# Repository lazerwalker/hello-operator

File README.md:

# Hello, Operator!

This is the source code that powers [Hello, Operator!](http://lazerwalker.com/hellooperator).

## Setup

1. Be sure you're using Node version `0.12.x`. This is because `node-serialport` won't compile on OS X on anything newer. I personally use [nvm](https://github.com/creationix/nvm) to manage this; it is also specified in `package.json`. It is possible newer versions of Node will work in non-OS X environments, but that has not been tested.

2. Install coffee-script globally: `npm install -g coffee-script`

3. Git clone this repo: `git clone git@github.com:lazerwalker/switchboard.git`

4. Install dependencies: `npm install`

5. Modify `runner.coffee` to include the appropriate game interfaces with appropriate options (e.g. Arduino USB serial ports)

6. Run `coffee runner.coffee`

## Audio

This repository does not currently contain the audio files used in the game. In order to play it, the "audio" folder will need data in the following structure: 

```
/ audio 
  / Ethel
    / Rosemary.aiff
    / Donald.aiff
  / Rosemary
    / Ethel.aiff
```

There must be a folder for every character in the game (defined in `game.coffee`), and each character's folder must contain an audio file called `{name}.aiff` for every other name.

It is likely that the actual audio used in the game itself will be released under a Creative Commons license at some point, but that is not the case at this time. Currently, this is accomplished via a private submodule; you will likely want to create your own submodule and update your internal git structure to point to it.

## iOS Project

To run the included iPad version of the game, you need to compile the codebase into a single JS file. Run `./compile` in the root directory, then run and compile the Xcode workspace that lives in the `ios` subdirectory. This will only work on OS X with the latest version of Xcode.

By default, the iOS app will just run the game itself. You can also use it as a remote client to a server-run instance of the game; that requires a deployment of the server component, which isn't currently documented. Sorry about that.

## Caveats

This codebase isn't in great shape. It's persisted across three very different hardware iterations, and probably should have been rewritten from the ground up by now. Due to the severe time constraints surrounding this project, software engineering quality has generally taken second place to hardware fabrication. There's a lot of bad code and a lot of dead code. Some of the more recent code does have tests, which can be run via `npm test`.

Similarly, and perhaps more relevant, this documentation is terrible. If you actually intend on getting this up and running, you'll probably need to bug me personally. I'm not exactly sure who I expect to actively try to use this repo, but in general I'm cool with people contacting me with questions about it. Feel free to shoot me an email at hellooperator@lazerwalker.com, or tweet at me @lazerwalker.

## License

This project is licensed under the MIT License.

Copyright (c) 2014-2016 Mike Lazer-Walker and MIT Media Lab

Permission is hereby granted, free of charge, to any person obtaining a copy of this software and associated documentation files (the "Software"), to deal in the Software without restriction, including without limitation the rights to use, copy, modify, merge, publish, distribute, sublicense, and/or sell copies of the Software, and to permit persons to whom the Software is furnished to do so, subject to the following conditions:

The above copyright notice and this permission notice shall be included in all copies or substantial portions of the Software.

THE SOFTWARE IS PROVIDED "AS IS", WITHOUT WARRANTY OF ANY KIND, EXPRESS OR IMPLIED, INCLUDING BUT NOT LIMITED TO THE WARRANTIES OF MERCHANTABILITY, FITNESS FOR A PARTICULAR PURPOSE AND NONINFRINGEMENT. IN NO EVENT SHALL THE AUTHORS OR COPYRIGHT HOLDERS BE LIABLE FOR ANY CLAIM, DAMAGES OR OTHER LIABILITY, WHETHER IN AN ACTION OF CONTRACT, TORT OR OTHERWISE, ARISING FROM, OUT OF OR IN CONNECTION WITH THE SOFTWARE OR THE USE OR OTHER DEALINGS IN THE SOFTWARE.

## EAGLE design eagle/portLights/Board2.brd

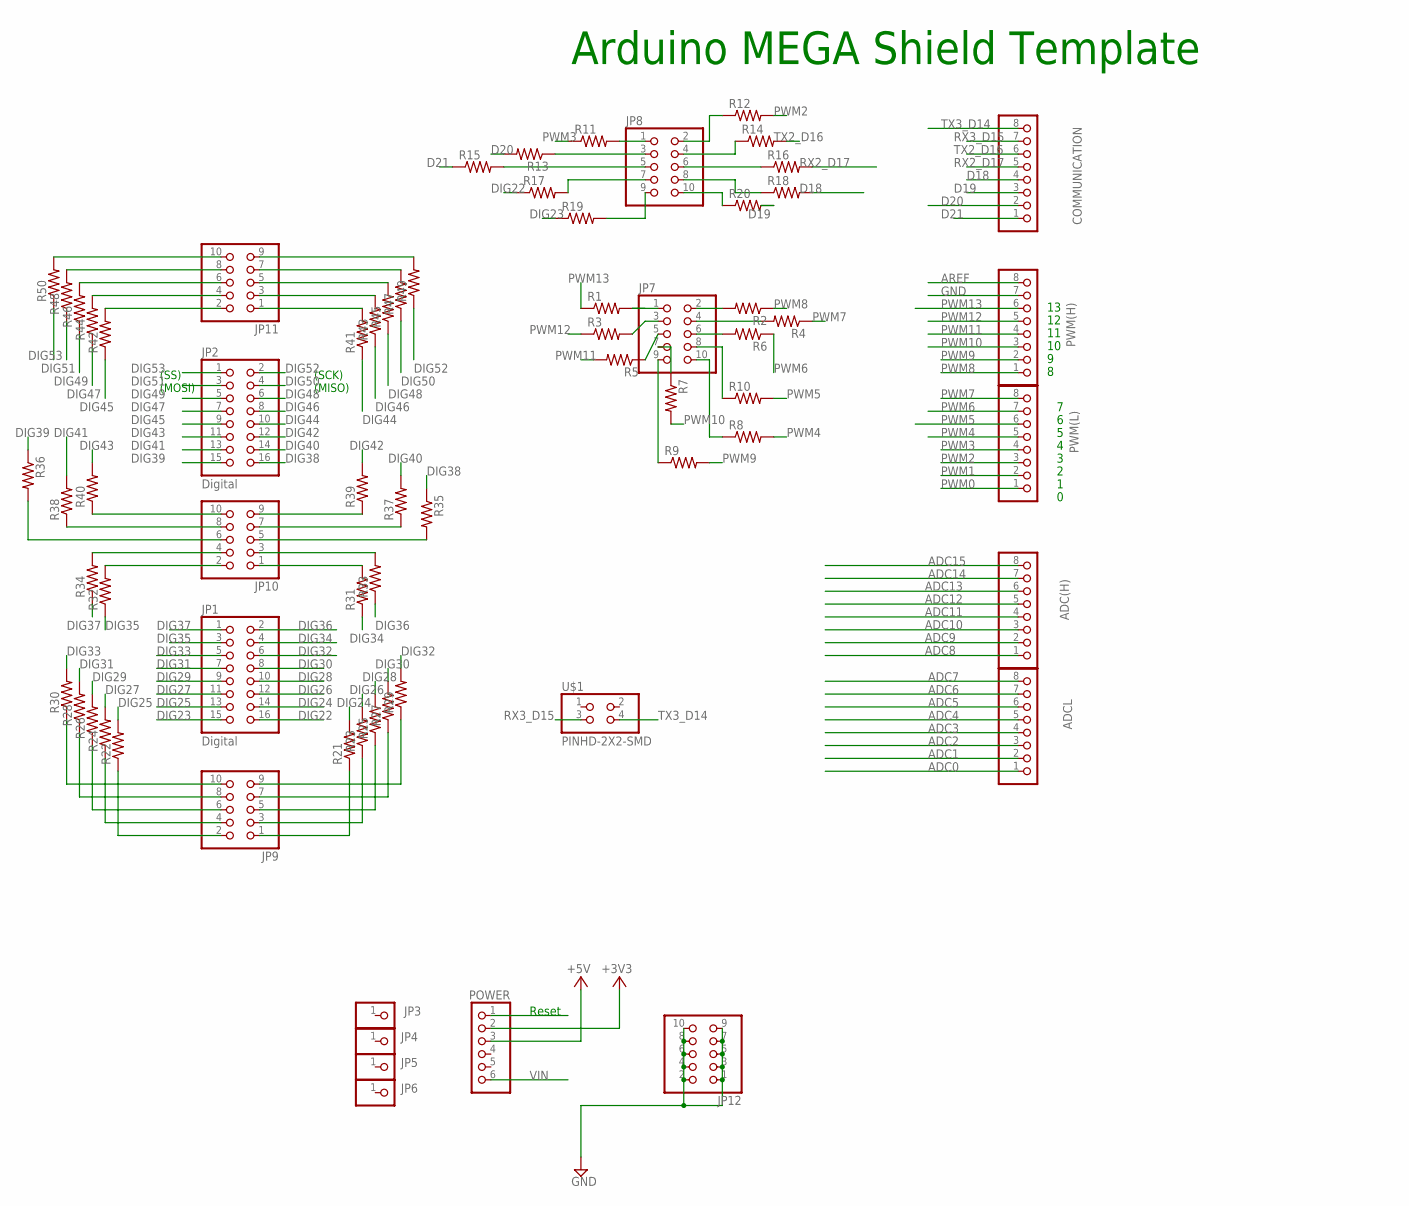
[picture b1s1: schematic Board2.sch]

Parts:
ADC(H): PINHD-1X8; 1X08
ADCL: PINHD-1X8; 1X08
COMMUNICATION: PINHD-1X8; 1X08
JP1, JP2: Digital; 2X08
JP3, JP4, JP5, JP6: PINHD-1X1; 1X01
JP7, JP8, JP9, JP10, JP11, JP12: PINHD-2X5SMT; 2X05_SMT
POWER: PINHD-1X6; 1X06
PWM(H): PINHD-1X8; 1X08
PWM(L): PINHD-1X8; 1X08
R1, R2, R3, R4, R5, R6, R7, R8, R9, R10, R11, R12, R13, R14, R15, R16, R17, R18, R19, R20, R21, R22, R23, R24, R25, R26, R27, R28, R29, R30, R31, R32, R33, R34, R35, R36, R37, R38, R39, R40, R41, R42, R43, R44, R45, R46, R47, R48, R49, R50: R-US_M1206; M1206
U$1: PINHD-2X2-SMD; 2X02SMD

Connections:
+3V3: POWER.2
+5V: POWER.3
ADC0: ADCL.1
ADC1: ADCL.2
ADC2: ADCL.3
ADC3: ADCL.4
ADC4: ADCL.5
ADC5: ADCL.6
ADC6: ADCL.7
ADC7: ADCL.8
ADC8: ADC(H).1
ADC9: ADC(H).2
ADC10: ADC(H).3
ADC11: ADC(H).4
ADC12: ADC(H).5
ADC13: ADC(H).6
ADC14: ADC(H).7
ADC15: ADC(H).8
AREF: PWM(H).8
D18: COMMUNICATION.4, R18.2
D19: COMMUNICATION.3, R20.2
D20: COMMUNICATION.2, R13.2
D21: COMMUNICATION.1, R15.1
DIG22: JP1.16, R17.1
DIG23: JP1.15, R19.1
DIG24: JP1.14, R21.2
DIG25: JP1.13, R22.2
DIG26: JP1.12, R23.2
DIG27: JP1.11, R24.2
DIG28: JP1.10, R25.2
DIG29: JP1.9, R26.2
DIG30: JP1.8, R27.2
DIG31: JP1.7, R28.2
DIG32: JP1.6, R29.2
DIG33: JP1.5, R30.2
DIG34: JP1.4, R31.1
DIG35: JP1.3, R32.1
DIG36: JP1.2, R33.1
DIG37: JP1.1, R34.1
DIG38: JP2.16, R35.1
DIG39: JP2.15, R36.1
DIG40: JP2.14, R37.2
DIG41: JP2.13, R38.2
DIG42: JP2.12, R39.2
DIG43: JP2.11, R40.2
DIG44: JP2.10, R41.1
DIG45: JP2.9, R42.1
DIG46: JP2.8, R43.1
DIG47: JP2.7, R44.1
DIG48: JP2.6, R45.1
DIG49: JP2.5, R46.1
DIG50: JP2.4, R47.1
DIG51: JP2.3, R48.1
DIG52: JP2.2, R49.1
DIG53: JP2.1, R50.1
GND: JP12.1, JP12.2, JP12.3, JP12.4, JP12.5, JP12.6, JP12.7, JP12.8, JP12.9, JP12.10, PWM(H).7
unnamed: JP7.3, R3.2
unnamed: JP7.5, R5.1
unnamed: JP7.7, R7.1
unnamed: JP7.9, R9.1
unnamed: JP7.4, R4.2
unnamed: JP8.5, R15.2
unnamed: JP7.6, R6.2
unnamed: JP7.2, R2.2
unnamed: JP7.8, R10.1
unnamed: JP8.1, R11.2
unnamed: JP8.2, R12.1
unnamed: JP7.10, R8.1
unnamed: JP8.7, R17.2
unnamed: JP10.6, R36.2
unnamed: JP8.6, R16.1
unnamed: JP10.5, R35.2
unnamed: JP8.4, R14.1
unnamed: JP9.2, R22.1
unnamed: JP7.1, R1.2
unnamed: JP8.10, R20.1
unnamed: JP9.4, R24.1
unnamed: JP9.6, R26.1
unnamed: JP9.8, R28.1
unnamed: JP9.10, R30.1
unnamed: JP9.1, R21.1
unnamed: JP9.3, R23.1
unnamed: JP9.5, R25.1
unnamed: JP9.7, R27.1
unnamed: JP9.9, R29.1
unnamed: JP10.3, R33.2
unnamed: JP10.1, R31.2
unnamed: JP10.2, R32.2
unnamed: JP10.4, R34.2
unnamed: JP10.7, R37.1
unnamed: JP10.9, R39.1
unnamed: JP10.8, R38.1
unnamed: JP10.10, R40.1
unnamed: JP11.9, R49.2
unnamed: JP11.7, R47.2
unnamed: JP11.5, R45.2
unnamed: JP11.3, R43.2
unnamed: JP11.1, R41.2
unnamed: JP11.2, R42.2
unnamed: JP11.4, R44.2
unnamed: JP11.6, R46.2
unnamed: JP11.8, R48.2
unnamed: JP11.10, R50.2
unnamed: JP8.9, R19.2
PWM0: PWM(L).1
PWM1: PWM(L).2
PWM2: PWM(L).3, R12.2
PWM3: PWM(L).4, R11.1
PWM4: PWM(L).5, R8.2
PWM5: PWM(L).6, R10.2
PWM6: PWM(L).7, R6.1
PWM7: PWM(L).8, R4.1
PWM8: PWM(H).1, R2.1
PWM9: PWM(H).2, R9.2
PWM10: PWM(H).3, R7.2
PWM11: PWM(H).4, R5.2
PWM12: PWM(H).5, R3.1
PWM13: PWM(H).6, R1.1
RESET: POWER.1
RX1_D19: JP8.8, R18.1
RX2_D17: COMMUNICATION.5, R16.2
RX3_D15: COMMUNICATION.7, U$1.3
RX4_D14: JP8.3, R13.1
TX2_D16: COMMUNICATION.6, R14.2
TX3_D14: COMMUNICATION.8, U$1.4
VIN: POWER.6

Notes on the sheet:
Arduino MEGA Shield Template
(SS)
(MOSI)
(SCK)
(MISO)
Reset

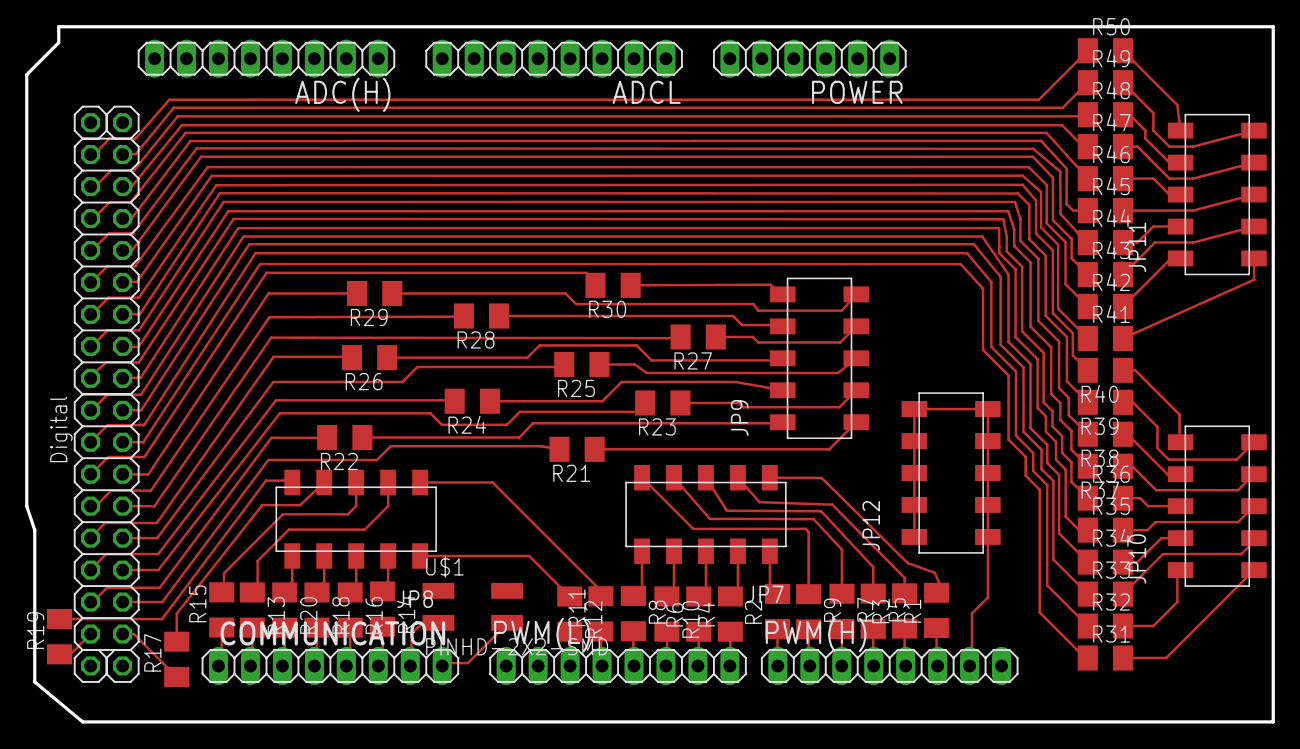
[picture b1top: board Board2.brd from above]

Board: 2 copper layers, 99.1 x 55.2 mm, 69 parts (0 on the bottom side), 103 nets.

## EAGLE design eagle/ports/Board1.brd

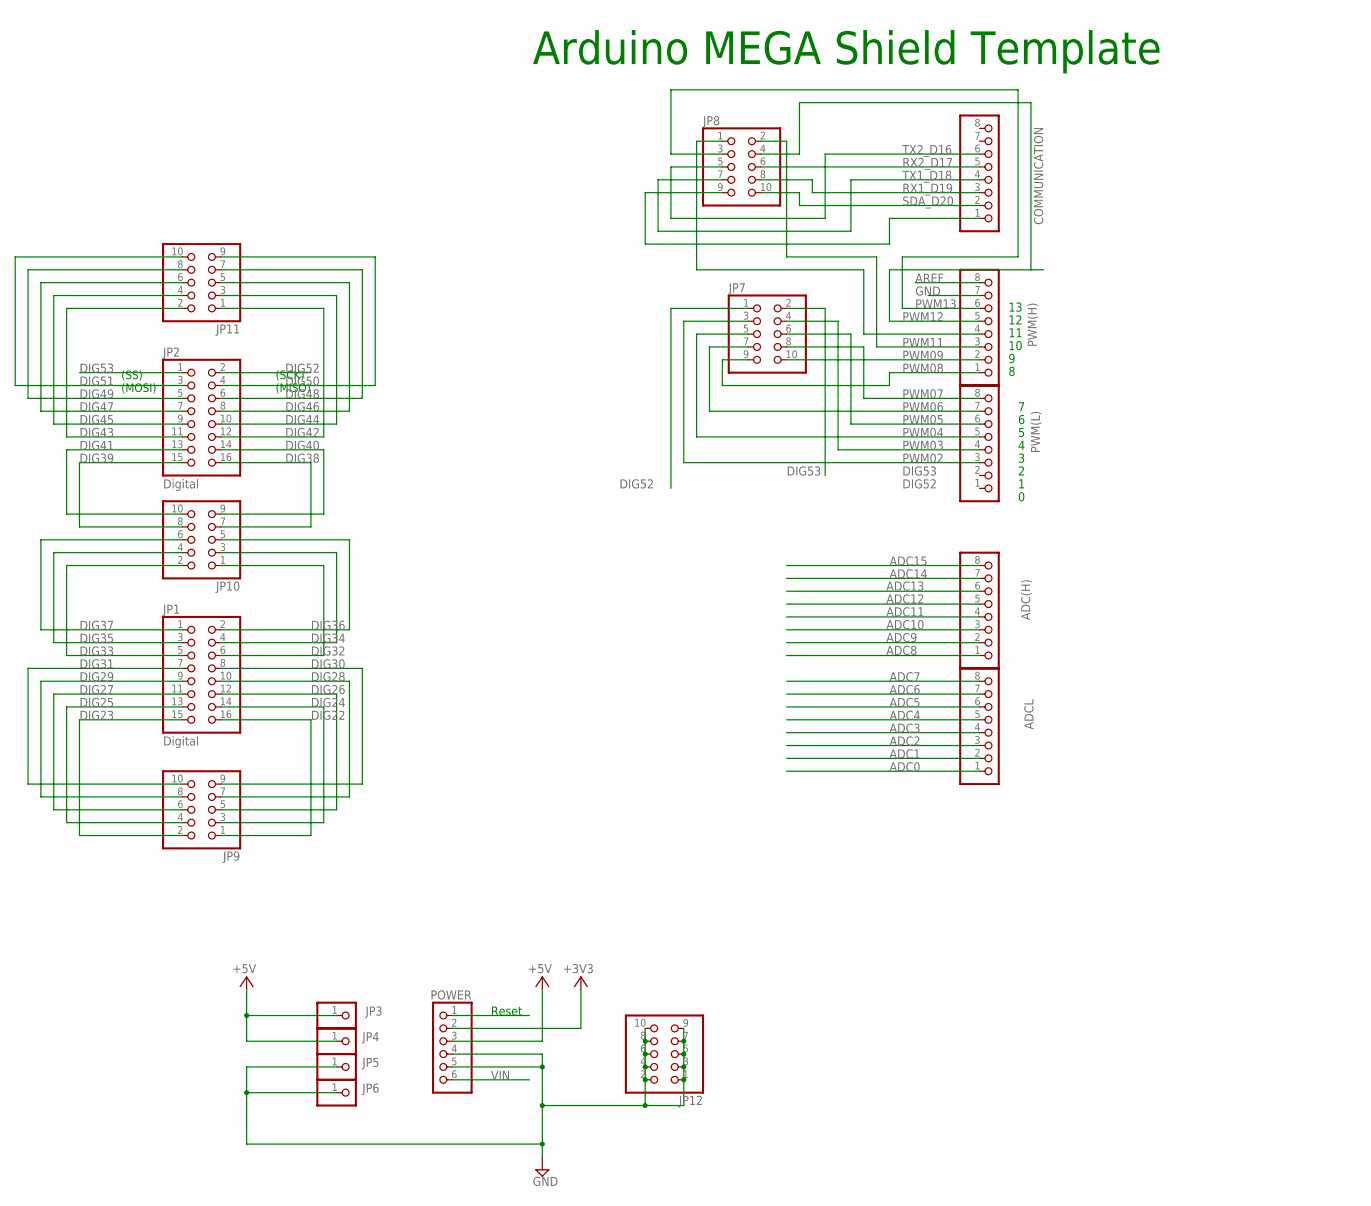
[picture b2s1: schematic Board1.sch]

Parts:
ADC(H): PINHD-1X8; 1X08
ADCL: PINHD-1X8; 1X08
COMMUNICATION: PINHD-1X8; 1X08
JP1, JP2: Digital; 2X08
JP3, JP4, JP5, JP6: PINHD-1X1; 1X01
JP7, JP8, JP9, JP10, JP11, JP12: PINHD-2X5SMT; 2X05_SMT
POWER: PINHD-1X6; 1X06
PWM(H): PINHD-1X8; 1X08
PWM(L): PINHD-1X8; 1X08

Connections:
+3V3: POWER.2
+5V: JP3.1, JP4.1, POWER.3
ADC0: ADCL.1
ADC1: ADCL.2
ADC2: ADCL.3
ADC3: ADCL.4
ADC4: ADCL.5
ADC5: ADCL.6
ADC6: ADCL.7
ADC7: ADCL.8
ADC8: ADC(H).1
ADC9: ADC(H).2
ADC10: ADC(H).3
ADC11: ADC(H).4
ADC12: ADC(H).5
ADC13: ADC(H).6
ADC14: ADC(H).7
ADC15: ADC(H).8
AREF: PWM(H).8
DIG22: JP1.16, JP9.1
DIG23: JP1.15, JP9.2
DIG24: JP1.14, JP9.3
DIG25: JP1.13, JP9.4
DIG26: JP1.12, JP9.5
DIG27: JP1.11, JP9.6
DIG28: JP1.10, JP9.7
DIG29: JP1.9, JP9.8
DIG30: JP1.8, JP9.9
DIG31: JP1.7, JP9.10
DIG32: JP1.6, JP10.1
DIG33: JP1.5, JP10.2
DIG34: JP1.4, JP10.3
DIG35: JP1.3, JP10.4
DIG36: JP1.2, JP10.5
DIG37: JP1.1, JP10.6
DIG38: JP2.16, JP10.7
DIG39: JP2.15, JP10.8
DIG40: JP2.14, JP10.9
DIG41: JP2.13, JP10.10
DIG42: JP2.12, JP11.1
DIG43: JP2.11, JP11.2
DIG44: JP2.10, JP11.3
DIG45: JP2.9, JP11.4
DIG46: JP2.8, JP11.5
DIG47: JP2.7, JP11.6
DIG48: JP2.6, JP11.7
DIG49: JP2.5, JP11.8
DIG50: JP2.4, JP11.9
DIG51: JP2.3, JP11.10
DIG52: JP2.2, JP7.1
DIG53: JP2.1, JP7.2
GND: JP5.1, JP6.1, JP12.1, JP12.2, JP12.3, JP12.4, JP12.5, JP12.6, JP12.7, JP12.8, JP12.9, JP12.10, POWER.4, POWER.5, PWM(H).7
unnamed: COMMUNICATION.2, JP8.10
PWM02: JP7.3, PWM(L).3
PWM03: JP7.4, PWM(L).4
PWM04: JP7.5, PWM(L).5
PWM05: JP7.6, PWM(L).6
PWM06: JP7.7, PWM(L).7
PWM07: JP7.8, PWM(L).8
PWM08: JP7.9, PWM(H).1
PWM09: JP7.10, PWM(H).2
PWM10: JP8.1, PWM(H).4
PWM11: JP8.2, PWM(H).3
PWM12: JP8.4, PWM(H).5
PWM13: JP8.3, PWM(H).6
RESET: POWER.1
RX1_D19: COMMUNICATION.3, JP8.8
RX2_D17: COMMUNICATION.5, JP8.6
SDA_D20: COMMUNICATION.1, JP8.9
TX1_D18: COMMUNICATION.4, JP8.7
TX2_D16: COMMUNICATION.6, JP8.5
VIN: POWER.6

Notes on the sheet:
Arduino MEGA Shield Template
(SS)
(MOSI)
(SCK)
(MISO)
Reset

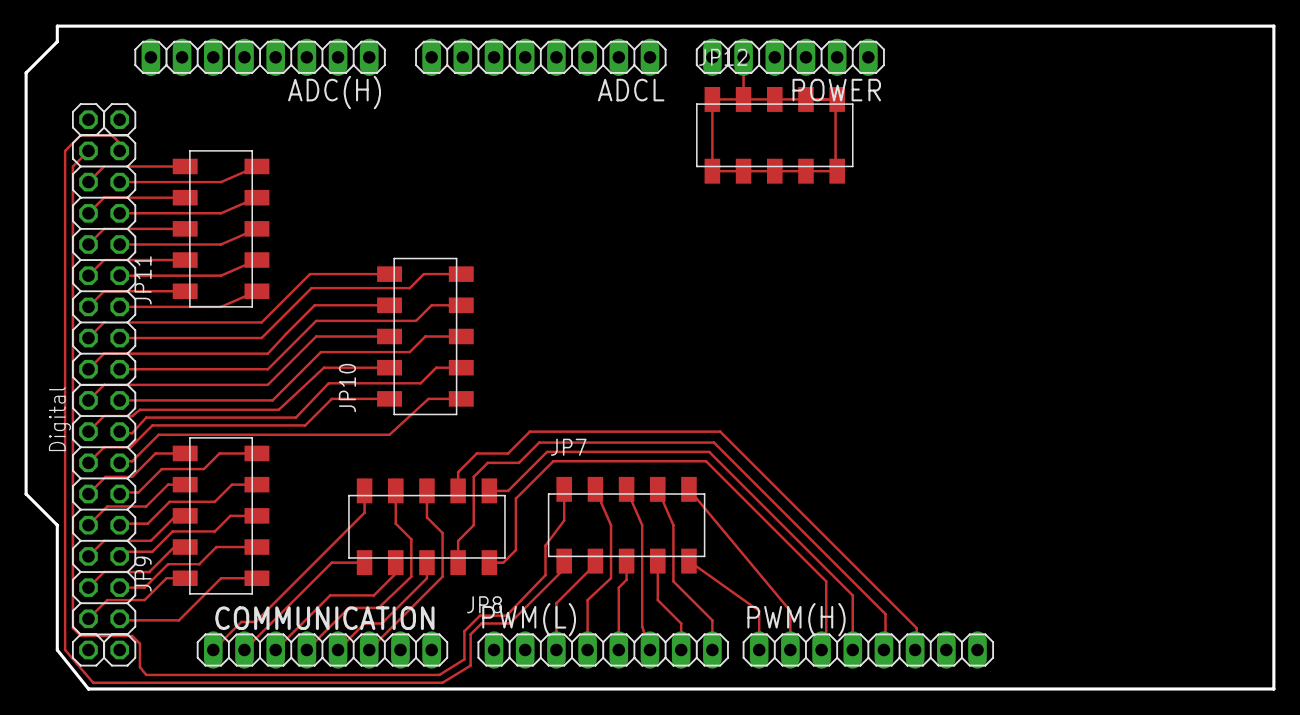
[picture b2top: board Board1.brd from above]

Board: 2 copper layers, 101.6 x 54.0 mm, 18 parts (0 on the bottom side), 52 nets.

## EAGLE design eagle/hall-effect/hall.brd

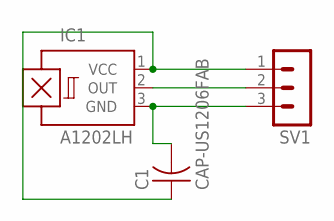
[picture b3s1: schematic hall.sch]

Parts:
C1: CAP-US1206FAB; C1206FAB
IC1: A1202LH; SOT23-W
SV1: MA03-1

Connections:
unnamed: C1.1, IC1.1 (VCC), SV1.1
unnamed: IC1.2 (OUT), SV1.2
unnamed: C1.2, IC1.3 (GND), SV1.3

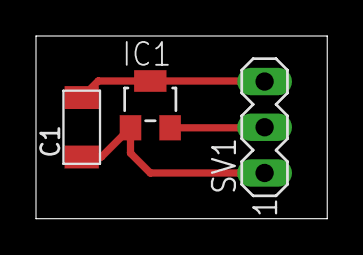
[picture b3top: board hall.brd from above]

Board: 2 copper layers, 16.2 x 10.1 mm, 3 parts (0 on the bottom side), 3 nets.

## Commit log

2014-10-11 Arduino script sends JSON
2014-10-11 CoffeeScript can read from serial port
2014-10-11 Change JSON format
2014-10-11 Fix bug interfering when multiple pins connected
2014-10-11 Install understore.js
2014-10-11 Switch from newline to carriage return
2014-10-11 Can pick up callers
2014-10-11 Add matching logic
2014-10-11 Don't let you double-pick-up
2014-10-11 Fix malformed serial parsing errors
2014-10-11 Switch from naive pin mapping to fuller objects
2014-10-11 Don't start call with people who are already busy
2014-10-11 2 rows of phones
2014-10-11 Can play audio
2014-10-11 Turn LEDs on/off as appropriate
2014-10-12 Tweaks to LED logic
2014-10-12 Make output easily togglable
2014-10-12 Don't let you complete the circuit without knowing who it is
2014-10-12 Remove LED testing code
2014-10-12 Change highest pin in arduino code
2015-08-24 Add gitignore
2015-08-24 move arduino stuff into its own folder
2015-08-24 Preliminary split-out interface work
2015-08-24 gitignore node_modules
2015-08-24 Game is playable with console interface
2015-08-24 Add (untested) WebsocketInterface
2015-08-24 Add iOS project
2015-08-24 Add SwiftWebSocket
2015-08-30 iOS app has a grid of things
2015-08-30 iOS gitignore
2015-08-30 Go from 8 to 10 ports on iOS
2015-08-30 Bind items
2015-08-30 Can set name and LED status
2015-08-30 Abstract game logic from game runner
2015-08-30 JS talks to iOS
2015-08-30 Game connection can talk to screen a bit
2015-08-31 Can highlight things
2015-08-31 Show who you're connected to
2015-08-31 Can use operator
2015-08-31 Can do full round-trip to iOS
2015-08-31 Light turns off after call connected
2015-08-31 Order doesn't matter when completing missions
2015-09-01 Remove websocket
2015-12-06 WIP?
2015-12-11 Update the things
2015-12-11 Changes to get RPi code working
2015-12-12 Re-enable second row
2015-12-14 Let plug detection work on RPi
2015-12-14 Remove unneeded this scoping workaround
2015-12-14 Add vim .swp files to gitignore
2015-12-15 Add basic charlieplexing example
2015-12-19 Add speech synthesis to iPad version
2015-12-19 Update iPad UI to match physical board
2015-12-19 Add 1920s female names
2015-12-19 Rename completeCall to askToDisconnect
2015-12-19 Switch iOS app to a drag interface
2015-12-19 Can drag to rearrange cables
2015-12-19 Abstract out connect/disconnect functionality in VC
2015-12-21 Add lines between connected parties
2015-12-21 Add nonfunctional switches
2015-12-28 Flash to indicate ready to disconnect a call
2015-12-28 Variable delay before call ends
2015-12-28 Add support for simultaneous calls
2015-12-28 Remove compiled JS from git
2015-12-29 Disconnecting calls flash to indicate frustration
2015-12-29 Lights also flash for frustration when asking to connect
2015-12-29 Add extra level of waiting
2015-12-29 Add random wait to add a new call
2015-12-29 Start new call when party is ready to disconnect, not after they do
2015-12-29 Add very simple increase in time intensity
2015-12-29 Very simple mechanism for adding more active calls over time
2015-12-29 Let the player rehear the operator speech
2016-01-30 Balance tweaks
2016-01-30 Lazy switch to portrait
2016-02-03 API operates on raw actions, not game mechanics
    Instead of things like "Charlie should ask to connect", the API now
    operates at the lower level of "Blink Charlie's LED at 500ms"
2016-02-05 Remove asking to disconnect
2016-02-05 Blinking people go solid after picking up
2016-02-06 iOS has UI to match hardware (but it's not wired up)
2016-02-06 Cable LEDs can illuminate
2016-02-06 iOS can connect to front/rear cables
2016-02-06 Reorganize Game class
2016-02-06 iOS switches are wired up
2016-02-07 Update console interface
2016-02-14 Switch to new state machine system with new flow
2016-02-14 Illuminate cable lights
2016-02-14 Remove dead code
2016-02-14 Move code into 'src' dir
2016-02-14 Create functioning compile script
2016-02-14 Fix cable ordering on client
2016-02-14 Start new calls when old ones finish, again
2016-02-14 Re-add increase in intensity
2016-02-14 Blink cable lights while ringing
2016-02-14 Make a bit easier for now
2016-02-24 A lot of WIP
2016-02-24 Add all working separate Arduino pieces
2016-02-25 Turn Arduino types into classes
2016-02-25 Create ArduinoGroup class to auto-assign types
    This is a single object that, given a list of serial ports, auto-creates
    a bunch of specific device types based on the identifier sent over
    serial.
2016-02-25 A whole lot of WIP
2016-02-25 ArduinoGroup emits 'ready' message
2016-02-25 Tweak pin numbers for cable
2016-02-25 ArduinoGroup logs port -> type mappings
2016-02-25 Cable and switch can be subscribed to
2016-02-25 Add WIP calibration script
2016-02-25 Calibration theoretically works for cables, ports, and switches
2016-02-25 Distinguish between port and plug lights at a software level
2016-02-25 Add OS X speak capability
2016-02-25 Stop switch ghosting
    For some weird hardware reason, flipping the rear switches to "talk" ghosts the equivalent front talk key.
    This adds in some debouncing, which is a hack but lets us fix it in
    software
2016-02-25 Fixes to names of things
2016-02-25 Switches are all wired up
2016-02-26 Add debug logs
2016-02-26 Add CableLights (renamed)
2016-02-26 Make light serial communication more robust
2016-02-26 Add calibration for cable lights
2016-02-26 Standardize calibration values, add illumination test
2016-02-27 Game sort of works
2016-02-27 Fix cable lights
2016-02-27 Add other 5 cables
2016-02-28 Switch to single powered hub
2016-02-28 Add intermediary WaitingToTalk state
2016-03-03 Add coffeeify as a dev dependency
2016-03-03 Add README with reminder to use node 0.12.10
2016-03-03 Add names file
2016-03-03 Update names
2016-03-03 Update iOS view
2016-03-03 Only use 5 cables for iOS
2016-03-03 Can stop game by flipping all front switches to talk
2016-03-03 Start a new game on restarting
2016-03-03 ArduinoGroup can be faked
2016-03-03 Add initial audio test
2016-03-06 iOS app has 10 cables
2016-03-06 Extract out generic GameInterface
2016-03-07 WebSocket client exists and works on iPad
2016-03-07 Resend list of names when a new client connects
2016-03-07 Clients can get updates on connect/disconnect/toggleSwitch from other clients
2016-03-07 Fix iOS port order
2016-03-07 Can re-hear a talk command
2016-03-07 Can change game type and server URL from iPad client
2016-03-07 Reset iPad game when changing types
2016-03-07 Add audio files
2016-03-07 Remove audio-playing bug
    When switching from 'talk' mode to 'neutral', the audio was re-playing.
    This fixes that.
2016-03-07 Fix missing iPad cable
2016-03-07 Fix audio re-trigger bug
    If you had the rear switch in Talk, and toggled the front switch, it
    would re-play
2016-03-07 Can't trigger ring while talk is active
2016-03-07 [iPad] Reset the game when people change
2016-03-07 Can't talk if someone else is talking
2016-03-15 Add server as a proper submodule
2016-03-16 In working state
2016-03-28 Let people talk while other talk keys are flipped
2016-03-28 Let ring switch work in either direction
2016-03-28 Fix reset functionality
2016-03-28 Fix bug from crashing
    This doesn't fix the underlying bug, it just stops the whole thing from
    crashing to a grinding halt when it somehow tries to do a thing with an
    undefined cable
2016-03-28 Tweak timing for calls
2016-03-28 Fix console logging for switch toggling
2016-03-28 Extract out game logic into GameMode
2016-03-28 Update README with license and setup instructions
2016-03-30 Add 'sayText' command to Interface
2016-03-30 Add test infrastructure
2016-03-30 Clean up repo
2016-03-30 Add tests for game mode API conformity
2016-03-30 Remove callingInterface from gameMode methods
2016-03-30 Add no-op tutorial mode
2016-03-30 Abstract out interface methods
    Instead of a Mode iterating through a Game's interfaces to do things like turn on
    lights, it can now just call a helper method on Game
2016-03-30 Start coding the tutorial
2016-04-07 Switch to using 'sfx' library for playing audio on Arduino
2016-04-07 Refactor API methods to use promises, and high-level game methods to join promises across all interfaces
2016-04-07 [Garbage] Update runner for testing
2016-04-11 Update pin numbers
2016-04-11 Update settings to match Members Week connection
2016-04-11 Workaround for weird ring bug
2016-04-11 Add attract mode
2016-04-11 Attract mode goes in a circle
2016-04-11 Re-set up runner for production
2016-04-11 Finesse attract mode
2016-04-11 Add devRunner
2016-04-11 Attempt to let attract mode -> game mode
2016-04-11 Fix attract mode transition
2016-04-11 Can reset properly to attract mode
2016-04-13 Add chai to devDependencies
2016-04-13 Specify node version
2016-04-13 Game auto-resets after 20 seconds
2016-04-13 Add info about audio
2016-04-13 Don't start a call where the first caller is plugged in
2016-04-15 When plugging in a caller, light will turn on if key is already set to talk
2016-04-15 Remove unused logic
2016-04-15 Move resetting logic out of the main game class
2016-04-15 Fix auto-reset to play well with new modes
2016-04-17 Remove accidentally-focused tests
2016-04-17 Remove unnecessary npm modules
2016-04-18 Add startWhenReady() function to Game
2016-04-18 WIP: Pseudo-code for tutorial flow
2016-04-18 Tutorial sort-of works, using Storyboard(!!!)
2016-04-18 Make tutorial Storyboard logic more idiomatic
2016-04-19 Tutorial happy path works
    Specifically, this adds in proper support for blinking lights, turning
    off lights, and delays
2016-04-20 Handle fail states in tutorial
2016-04-27 Tutorial properly turns on cable lights
2016-04-27 Remove tutorial error causing false negatives
2016-04-27 Make some tutorial text slightly clearer
2016-04-27 Tutorial should ignore Franklin
    "Franklin" connections happen because of a physical short. This
    shouldn't ever be desired in the tutorial.
2016-04-27 Move tutorial after attract mode
2016-04-27 Add audio for tutorial
2016-04-27 Update tutorial.json to reflect actual text being spoken
2016-04-27 Allow ArduinoInterface to fall back to OS X speech synthesis for sayText
2016-04-27 Properly turn off Mabel's lights in the tutorial
2016-04-27 Update audio
2016-04-27 Add tutorial pause after Mabel talks but before tutorial continues
2016-04-28 Add Eagle files
2016-04-28 Redesign board 1 (non-LED board)
    This contains 3 major changes:
    * Pins 0 and 1 (TX/RX) are no longer used as data pins
    * SMD components are used for the 2x5 headers
    * 3.3v and 5v power breakouts are dropped in favor of making the 2x5 GND
    connection be omnidirectional
2016-04-29 Reset using rear switches, not front
2016-04-29 Let the game ignore broken ports
2016-04-29 Can skip the tutorial
2016-05-02 Update reset timeout to 30s
2016-05-03 Add untested rotary sketch
2016-05-03 Cable sketch can use any port number
2016-05-03 Remove unused Arduino sketches
2016-05-04 Add functioning rotary sketch
2016-05-06 Attempted fix at 'Franklin' ghosting issues
2016-05-06 Make cable port-scanning more memory-efficient
    The previous approach saw some unexpected behavior because it was so close to the memory limit of the Arduino. This simpler version works better!
2016-05-06 Added new attempt at 'Franklin' bug, that sort of works
2016-05-07 Prototype detecting phone pickup using Hall Effect sensor + magnets
2016-05-07 Hall Effect board uses through-hole cables instead of header pins
2016-05-08 Abstract out Hall Effect behavior into a C++ class
2016-05-08 Extract out rotary code to its own class
2016-05-08 WIP: Move rotary and hall effect sensors onto switches board
2016-05-21 Update tutorial to use new storyboard features
2016-05-21 Add missing underscore require
2016-05-21 Fixes to consoleInterface
2016-05-21 Revert "Update tutorial to use new storyboard features"
    This reverts commit 1c20c6cc249c8c70e900d49240102c44b453cdb5.
2016-06-06 Add untracked audio
2016-06-06 Bump devRunner
2016-06-08 Redesign portLights board
